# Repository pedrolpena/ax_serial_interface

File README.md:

# ax_serial_interface
A USB interface for the equipment used on our AX XBT lines.

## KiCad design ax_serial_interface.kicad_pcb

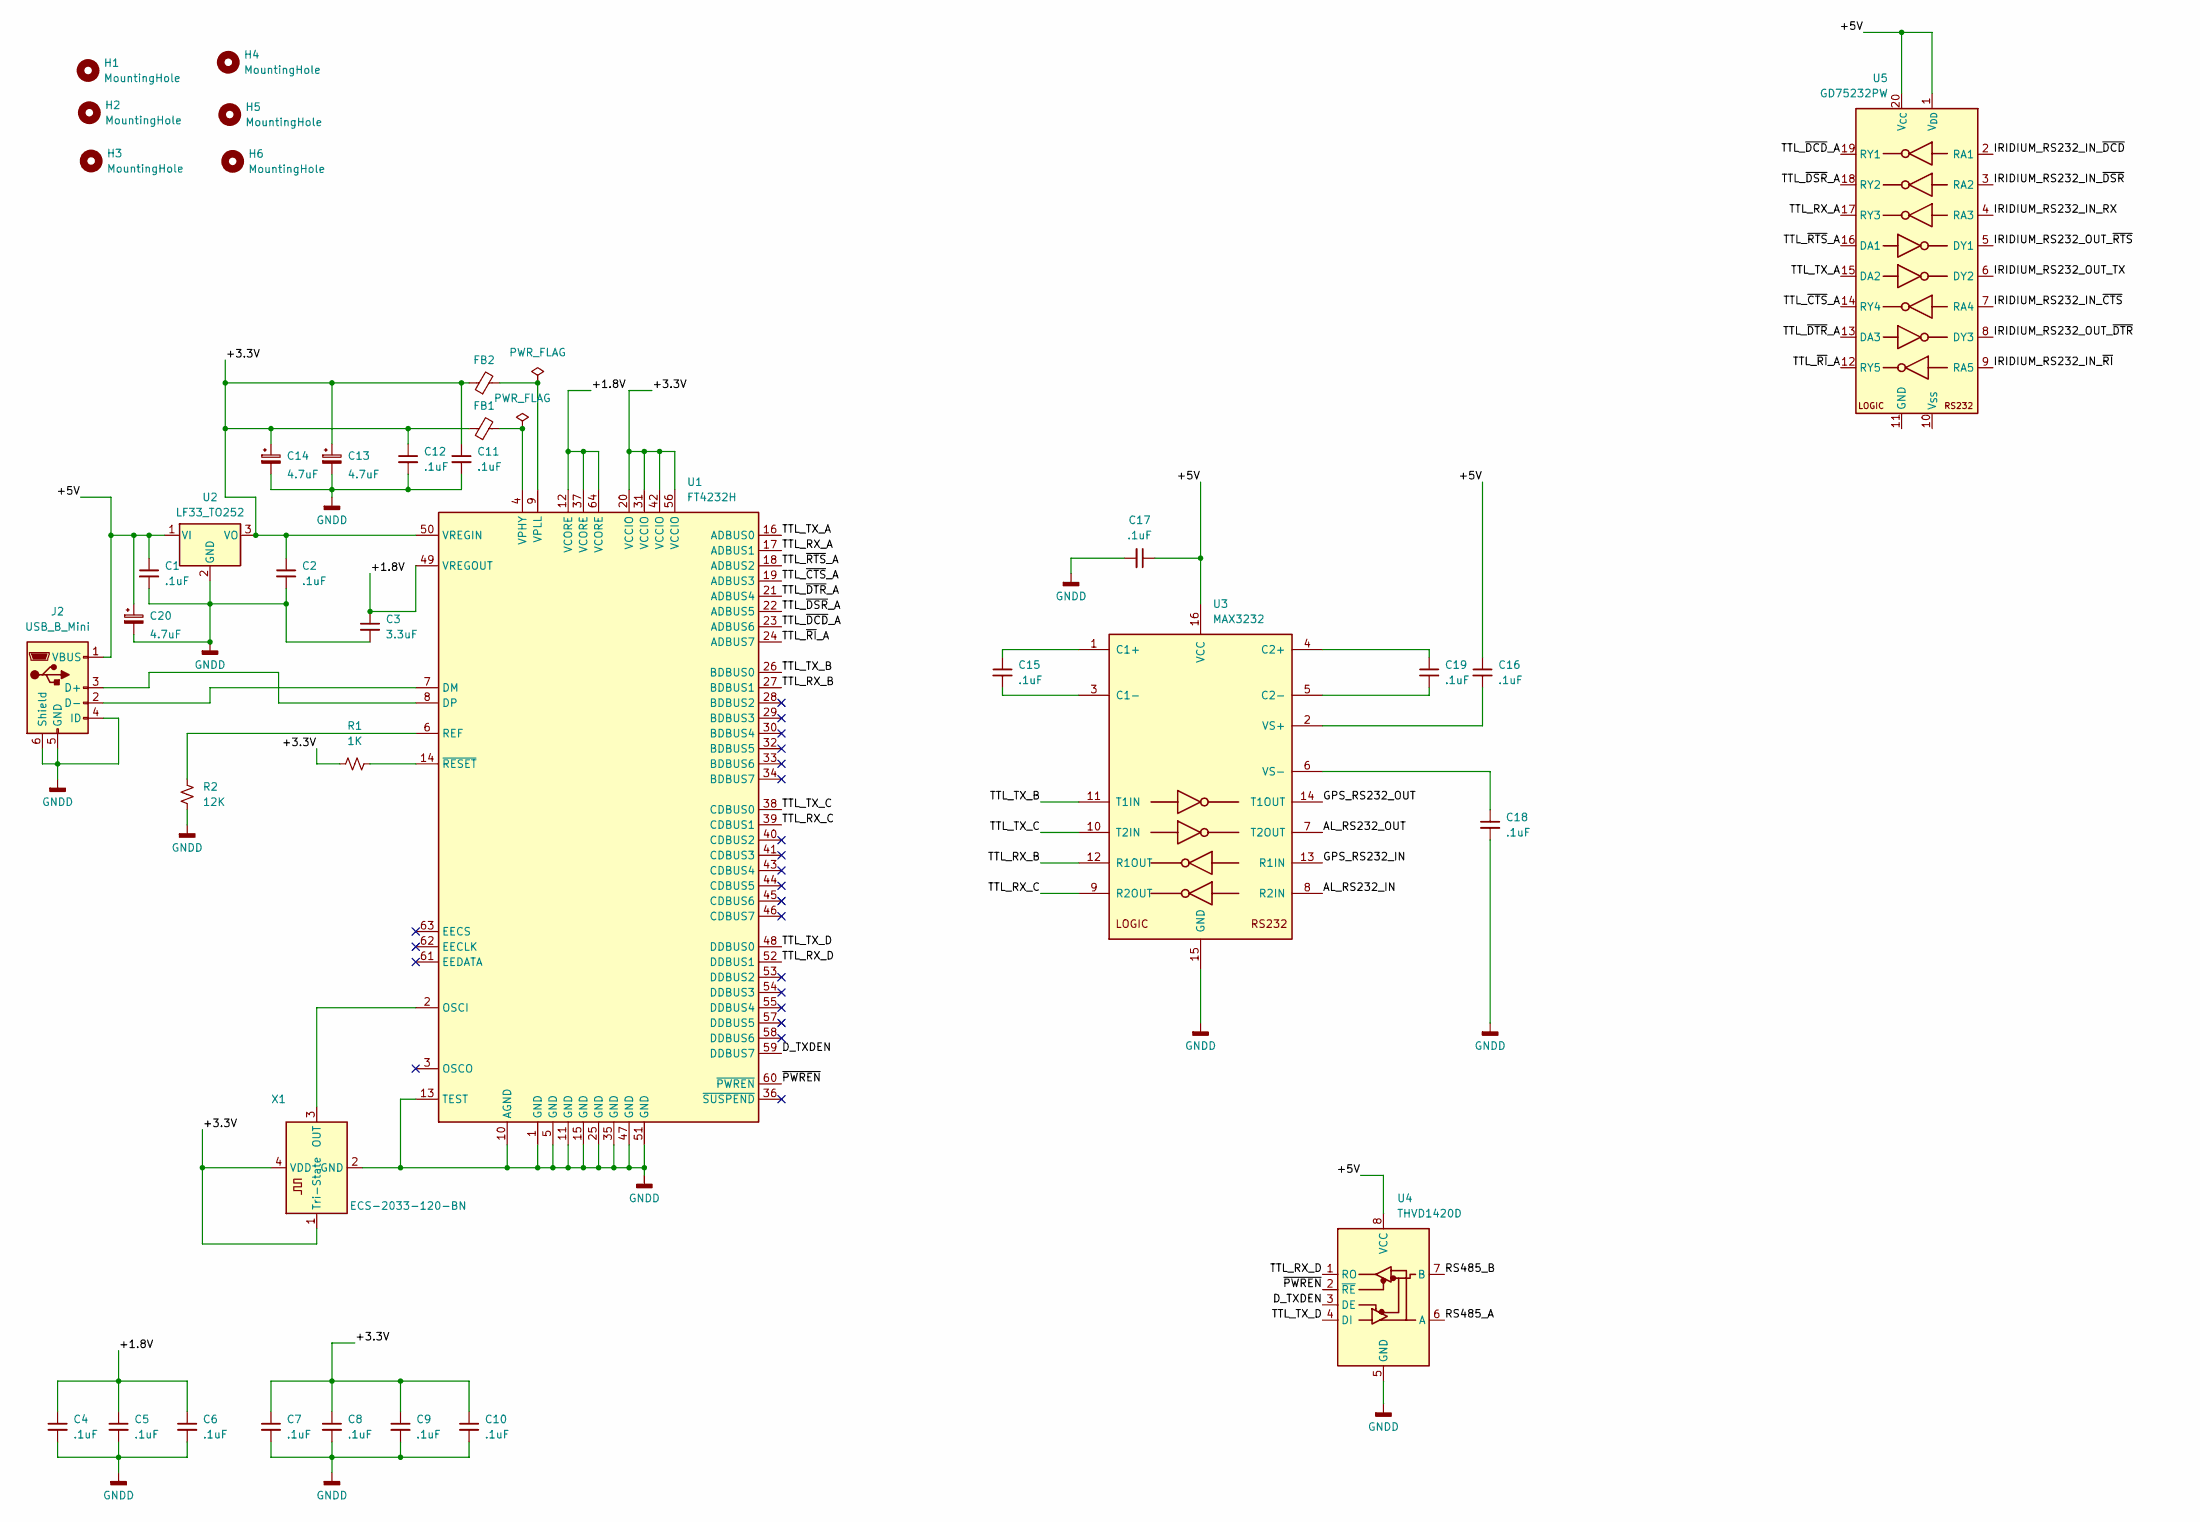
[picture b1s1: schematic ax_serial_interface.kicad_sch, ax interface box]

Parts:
C1, C2, C4, C5, C6, C7, C8, C9, C10, C11, C12, C15, C16, C17, C18, C19: .1uF; C_0805_2012Metric_Pad1.18x1.45mm_HandSolder; manufacturer part# CC0805KRX7R9BB104
C3: 3.3uF; C_0805_2012Metric_Pad1.18x1.45mm_HandSolder; manufacturer part# CGA4J1X7R1E335K125AC
C13, C14, C20: 4.7uF; CP_EIA-2012-12_Kemet-R_Pad1.30x1.05mm_HandSolder; manufacturer part# TAJR475M010RNJ
FB1, FB2: FerriteBead_Small; L_0805_2012Metric_Pad1.15x1.40mm_HandSolder; manufacturer part# HZ0805E601R-10
H1, H2, H3, H4, H5, H6: MountingHole; MountingHole_3.2mm_M3
J2: USB_B_Mini; USB_Mini-B_Wuerth_65100516121_Horizontal; manufacturer part# 65100516121
R1: 1K; R_0805_2012Metric_Pad1.20x1.40mm_HandSolder; manufacturer part# RC0805FR-071KL
R2: 12K; R_0805_2012Metric_Pad1.20x1.40mm_HandSolder; manufacturer part# RMCF0805JT12K0
U1: FT4232H; LQFP-64_10x10mm_P0.5mm; manufacturer part# FT4232HL-REEL
U2: LF33_TO252; TO-252-3_TabPin2; manufacturer part# BA033CC0FP-E2
U3: MAX3232; TSSOP-16_4.4x5mm_P0.65mm; Manufacturer part# MAX3232EUE+T
U4: THVD1420D; SOIC-8_3.9x4.9mm_P1.27mm; Manufacturer part# THVD1420DR
U5: GD75232PW; TSSOP-20_4.4x6.5mm_P0.65mm; Manufacturer part# GD75232PWR
X1: ECS-2033-120-BN; Oscillator_SMD_ECS_2520MV-xxx-xx-4Pin_2.5x2.0mm; manufacturer part# ECS-2033-120-BN

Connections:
/+1.8V: C3.1, C4.1, C5.1, C6.1, U1.12 (VCORE), U1.37 (VCORE), U1.49 (VREGOUT), U1.64 (VCORE)
/+3.3V: C2.1, C7.1, C8.1, C9.1, C10.1, C11.1, C12.1, C13.1, C14.1, FB1.1, FB2.1, R1.2, U1.20 (VCCIO), U1.31 (VCCIO), U1.42 (VCCIO), U1.50 (VREGIN), U1.56 (VCCIO), U2.3 (VO), X1.1 (Tri-State), X1.4 (VDD)
/+5V: C1.1, C16.1, C17.1, C20.1, J2.1 (VBUS), U2.1 (VI), U3.16 (VCC), U4.8 (VCC), U5.1 (V_{DD}), U5.20 (V_{CC})
/AL_RS232_IN: U3.8 (R2IN)
/AL_RS232_OUT: U3.7 (T2OUT)
/D_TXDEN: U1.59 (DDBUS7), U4.3 (DE)
/GPS_RS232_IN: U3.13 (R1IN)
/GPS_RS232_OUT: U3.14 (T1OUT)
/IRIDIUM_RS232_IN_RX: U5.4 (RA3)
/IRIDIUM_RS232_IN_~CTS: U5.7 (RA4)
/IRIDIUM_RS232_IN_~DCD: U5.2 (RA1)
/IRIDIUM_RS232_IN_~DSR: U5.3 (RA2)
/IRIDIUM_RS232_IN_~RI: U5.9 (RA5)
/IRIDIUM_RS232_OUT_TX: U5.6 (DY2)
/IRIDIUM_RS232_OUT_~DTR: U5.8 (DY3)
/IRIDIUM_RS232_OUT_~RTS: U5.5 (DY1)
/RS485_A: U4.6 (A)
/RS485_B: U4.7 (B)
/TTL_RX_A: U1.17 (ADBUS1), U5.17 (RY3)
/TTL_RX_B: U1.27 (BDBUS1), U3.12 (R1OUT)
/TTL_RX_C: U1.39 (CDBUS1), U3.9 (R2OUT)
/TTL_RX_D: U1.52 (DDBUS1), U4.1 (RO)
/TTL_TX_A: U1.16 (ADBUS0), U5.15 (DA2)
/TTL_TX_B: U1.26 (BDBUS0), U3.11 (T1IN)
/TTL_TX_C: U1.38 (CDBUS0), U3.10 (T2IN)
/TTL_TX_D: U1.48 (DDBUS0), U4.4 (DI)
/TTL_~CTS_A: U1.19 (ADBUS3), U5.14 (RY4)
/TTL_~DCD_A: U1.23 (ADBUS6), U5.19 (RY1)
/TTL_~DSR_A: U1.22 (ADBUS5), U5.18 (RY2)
/TTL_~DTR_A: U1.21 (ADBUS4), U5.13 (DA3)
/TTL_~RI_A: U1.24 (ADBUS7), U5.12 (RY5)
/TTL_~RTS_A: U1.18 (ADBUS2), U5.16 (DA1)
/~PWREN: U1.60 (~PWREN), U4.2 (~RE)
GNDD: C1.2, C2.2, C3.2, C4.2, C5.2, C6.2, C7.2, C8.2, C9.2, C10.2, C11.2, C12.2, C13.2, C14.2, C17.2, C18.2, C20.2, J2.4 (ID), J2.5 (GND), J2.6 (Shield), R2.2, U1.1 (GND), U1.5 (GND), U1.10 (AGND), U1.11 (GND), U1.13 (TEST), U1.15 (GND), U1.25 (GND), U1.35 (GND), U1.47 (GND), U1.51 (GND), U2.2 (GND), U3.15 (GND), U4.5 (GND), X1.2 (GND)
unnamed: J2.3 (D+), U1.8 (DP)
unnamed: J2.2 (D-), U1.7 (DM)
unnamed: U1.2 (OSCI), X1.3 (OUT)
unnamed: R2.1, U1.6 (REF)
unnamed: FB1.2, U1.4 (VPHY)
unnamed: FB2.2, U1.9 (VPLL)
unnamed: R1.1, U1.14 (~RESET)
unnamed: C15.1, U3.1 (C1+)
unnamed: C15.2, U3.3 (C1-)
unnamed: C19.1, U3.4 (C2+)
unnamed: C19.2, U3.5 (C2-)
unnamed: C16.2, U3.2 (VS+)
unnamed: C18.1, U3.6 (VS-)

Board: 2 copper layers, 37 parts (0 on the bottom side), 33 nets, no tracks yet.
